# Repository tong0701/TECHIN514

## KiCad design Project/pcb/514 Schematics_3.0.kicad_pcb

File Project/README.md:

# Desk Guardian
### Proximity-based Workspace Awareness System
**TECHIN 514 · Taya (Xintong) Li**

---

## Overview

Desk Guardian is a two-device IoT system that detects how close someone is to your desk and communicates that proximity through a physical gauge and ambient LED — passively, without any interaction required.

In shared workspaces, personal boundaries are often invisible. There is no ambient signal that tells others whether someone is available or focused. Desk Guardian solves this by turning proximity data into a real-time physical display.

---

## System Architecture

Two XIAO ESP32C3 devices communicate over BLE. The sensor device reads distance and classifies proximity state; the display device receives the state and updates the motor pointer and LED accordingly.

```
Sensor Device (BLE Client)          Display Device (BLE Server)
──────────────────────────          ───────────────────────────
XIAO ESP32C3                        XIAO ESP32C3
HC-SR04 Ultrasonic Sensor           28BYJ-48 Stepper Motor + ULN2003
Custom PCB + LiPo Battery           RGB LED + Push Button
                                    Custom PCB + LiPo Battery

TRIG → D9   ECHO → D8               Motor → D0–D3
                                    LED   → D4–D6
                                    BTN   → D10
```

**BLE Config**
- Service UUID: `6f4e0001-1111-2222-3333-444455556666`
- Characteristic UUID: `6f4e0002-1111-2222-3333-444455556666`
- Device name: `Taya_Display_Server`

---

## Proximity States & Logic Flow

| State | Distance | LED | Motor |
|-------|----------|-----|-------|
| SAFE | > 150 cm | Blue (solid) | Pointer left |
| APPROACHING | 45–150 cm | Red (blink) | Pointer center |
| TOO CLOSE | < 45 cm | Red (solid) | Pointer right |

**Auto-reset:** TOO CLOSE held for 3s with no change → auto-send APPROACHING + 5s cooldown. If person leaves → immediate reset to SAFE.

**Hysteresis:** TOO CLOSE exits at > 60 cm · SAFE exits at < 130 cm — prevents state flickering at threshold boundaries.

---

## Hardware

### Sensor Device

### Display Device

| Component | Qty | Notes |
|-----------|-----|-------|
| Seeed Studio XIAO ESP32C3 | 2 | One per device |
| HC-SR04 Ultrasonic Sensor | 1 | Sensor device |
| 28BYJ-48 Stepper + ULN2003 | 1 | Display device |
| 3.7V 1000mAh LiPo Battery | 2 | One per device |
| Custom PCB | 2 | KiCad, lab-fabricated |
| RGB LED | 1 | Display device (green channel non-functional in v1) |
| Push Button | 1 | On/off toggle |

**Power note:** Display device draws ~340mA peak (stepper active). USB power required during use. Future iteration will upsize battery capacity.

---

## Build Photos

| Both Devices | Sensor PCB | Sensor PCB |
|---|---|---|
|  |  |  |

| Display Internal | Display Internal | Sensor Enclosure |
|---|---|---|
|  |  |  |

| Display Enclosure | Display Enclosure |
|---|---|
|  |  |

---

## Signal Processing Pipeline

1. **Read** — HC-SR04 polled every 100ms via TRIG/ECHO GPIO
2. **Smooth** — 3-sample moving average; timeouts filled with last valid reading
3. **Classify** — State machine with hysteresis applied
4. **Send** — BLE characteristic write, only on state change

---

## Build & Flash

Both devices use PlatformIO with Arduino framework.

```ini
[env:seeed_xiao_esp32c3]
platform = espressif32
board = seeed_xiao_esp32c3
framework = arduino
monitor_speed = 115200
```

Flash display device first, then sensor. Sensor will scan for `Taya_Display_Server` on boot and connect automatically.

---

## Repository Structure

```
Project/
├── README.md
├── code/
│   ├── sensor/          # BLE client, HC-SR04 distance detection
│   │   ├── main.cpp
│   │   └── platformio.ini
│   └── display/         # BLE server, stepper + LED control
│       ├── main.cpp
│       └── platformio.ini
├── schematic/           # KiCad schematic files
├── pcb/                 # KiCad PCB layout files
├── cad/                 # 3D print STL files
├── ppt/                 # Final presentation
├── images/              # Device photos
├── datasheet/           # Component datasheets
└── archive/             # Original proposal and early schematics
```

---

## Known Issues & Future Work

- **Power** — Display device requires USB power; LiPo capacity needs to be upsized
- **Enclosure** — Display enclosure too large; USB port opening at wrong height; sensor aperture too small in v1
- **LED** — Green channel non-functional in v1; limited to red/blue only
- **Thresholds** — Distance thresholds are environment-dependent; future version should support configurable parameters or auto-calibration
- **BLE** — Occasional disconnects; auto-reconnect to be implemented

---

## Demo

[Video Demo](https://drive.google.com/file/d/1y1JuozKeC6GTdT54zdWIaoLAR-elOvjI/view?usp=drive_link)

---

## Original Proposal

[View archived proposal](archive/archive_proposal)

---

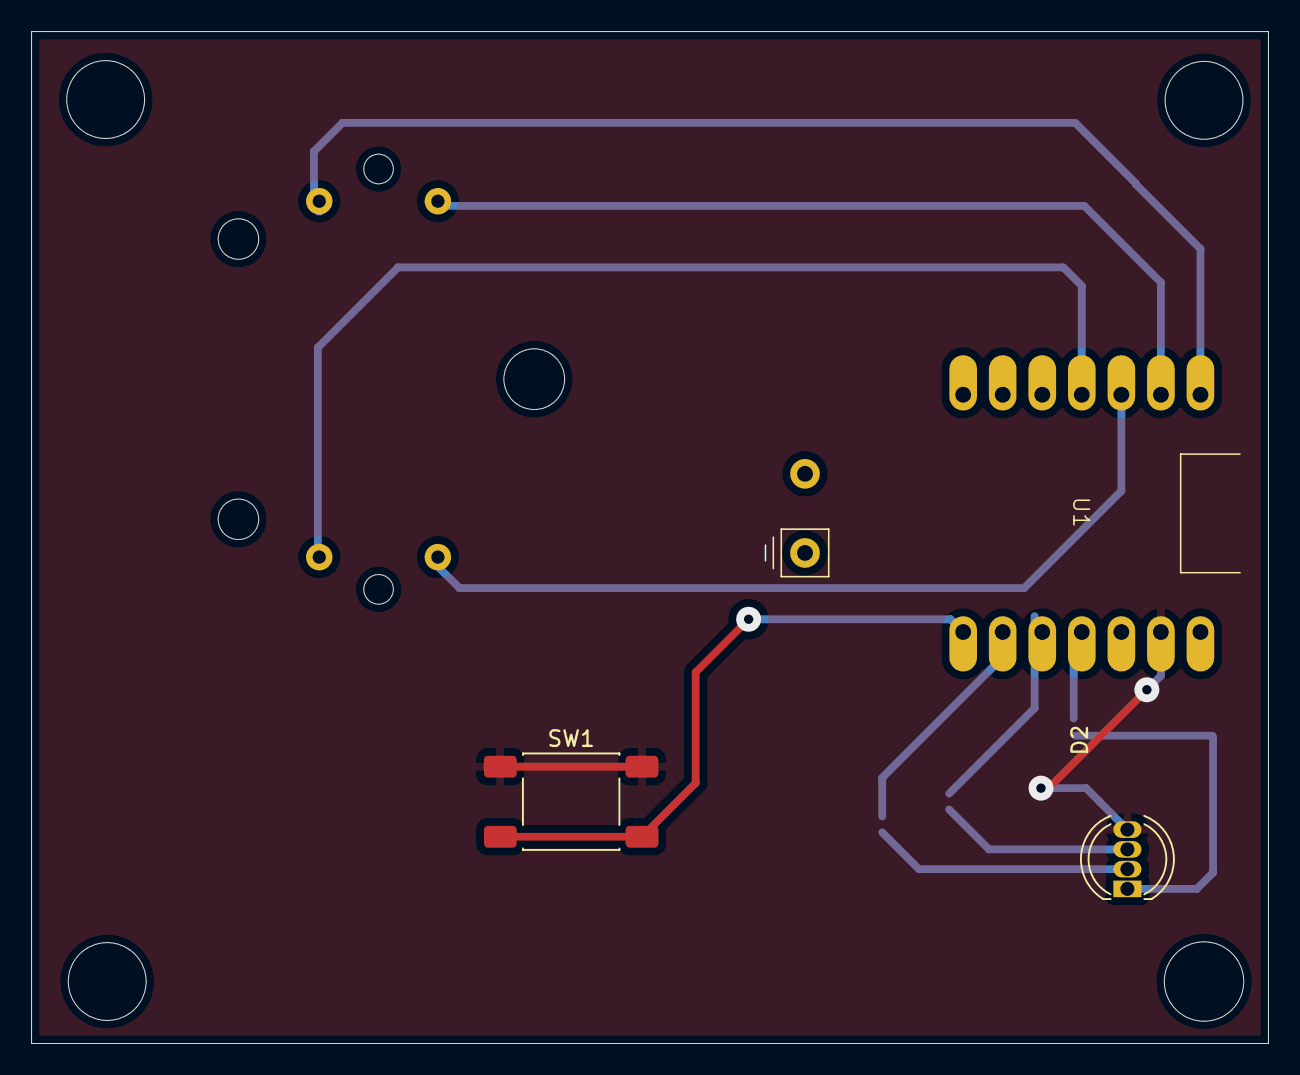
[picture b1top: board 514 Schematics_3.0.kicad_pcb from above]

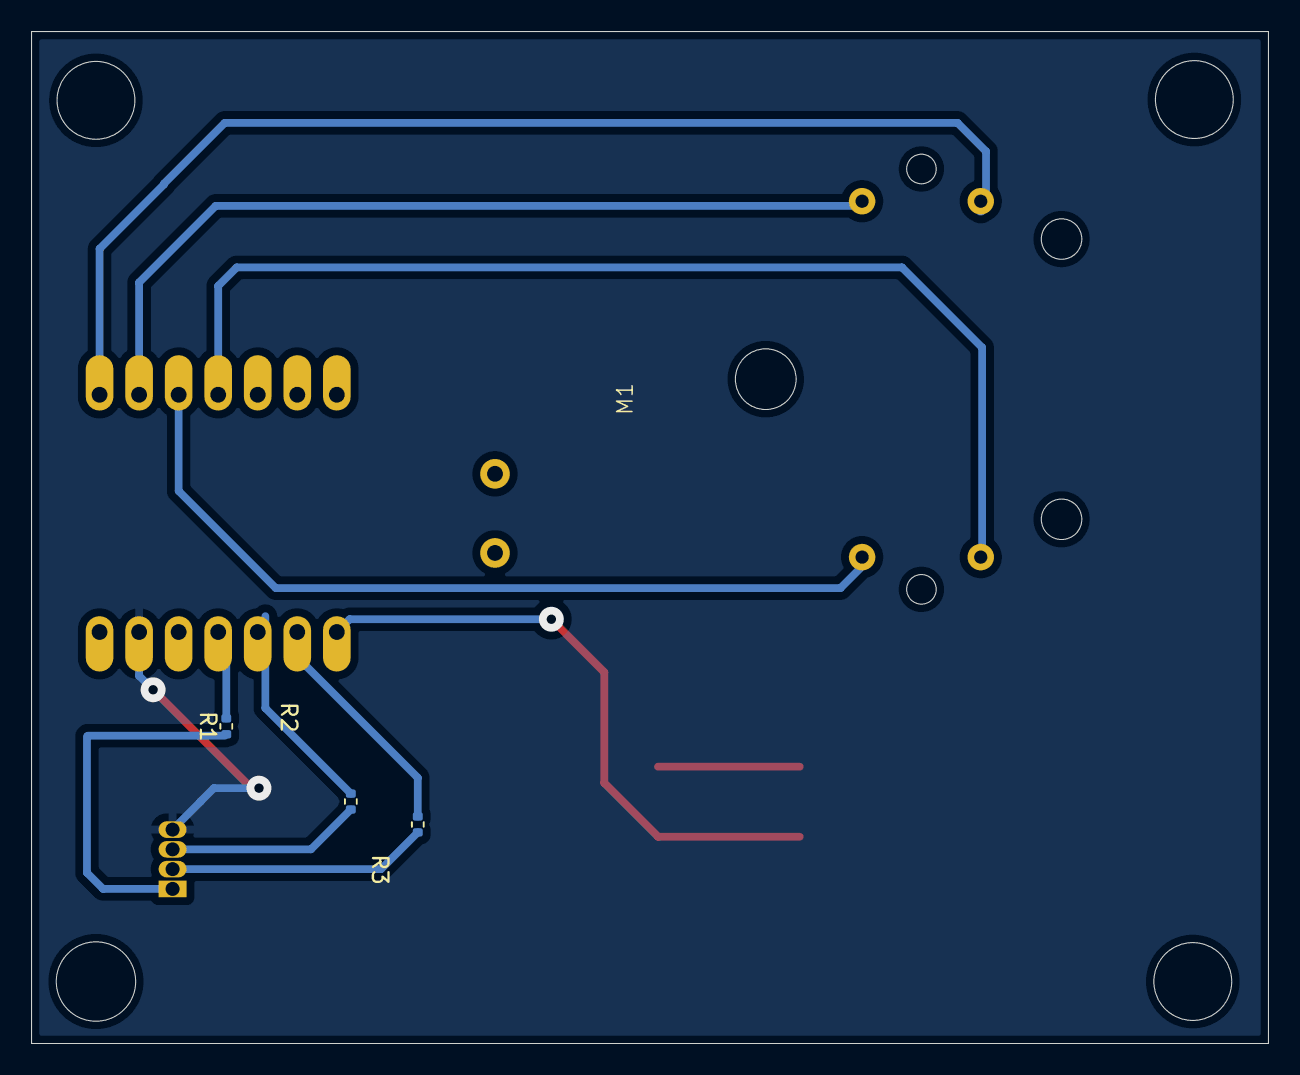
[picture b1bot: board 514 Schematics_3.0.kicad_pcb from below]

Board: 2 copper layers, 79.4 x 65.0 mm, 7 parts (4 on the bottom side), 12 nets.

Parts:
D2: LED_RBGA; LED_D5.0mm-4_RGB
M1: Stepper_Motor_bipolar; x27_stepper_two_holes
R1, R2, R3: R_Small; R_0402_1005Metric
SW1: SW_Push; SW_Push_1P1T_NO_E-Switch_TL3301NxxxxxG
U1: XIAO_ESP32

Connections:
GND: D2.4 (A), SW1.1, U1.13 (GND)
unnamed: D2.2 (BK), R3.1
unnamed: D2.3 (GK), R2.1
unnamed: D2.1 (RK), R1.1
unnamed: M1.2 (-), U1.1 (GPIO1_A0_D0)
unnamed: M1.1, U1.2 (GPIO2_A1_D1)
unnamed: M1.3, U1.3 (GPIO3_A2_D2)
unnamed: M1.4, U1.4 (GPIO4_A3_D3)
unnamed: R3.2, U1.9 (GPIO7_A8_D8_SCK)
unnamed: R2.2, U1.10 (GPIO8_A9_D9_CIPO)
unnamed: R1.2, U1.11 (GPIO9_A10_D10_COPI)
unnamed: SW1.2, U1.8 (GPIO44_D7_RX)

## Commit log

2026-01-05 Add Lab 1 required files
2026-01-05 Clean README for Lab 1
2026-01-05 Remove note about changing board configuration
2026-01-14 Add platformio.ini for Seeed Xiao ESP32C3
2026-01-20 Create 1
2026-01-20 Create noname
2026-01-20 Create 0
2026-01-20 Create techin514_final_sensor_pcb
2026-01-28 Create nonamee
2026-01-28 Create 11
2026-02-07 Add files via upload
    last version
2026-02-12 Create lightbroad
2026-02-22 Create 1.
2026-03-01 Add sensor code for distance measurement and ESP-NOW
2026-03-16 Add desk_guardian_final project for TECHIN514
2026-03-16 Restructure Project: archive old proposal and schematics, promote final project structure
2026-03-16 Rename README (2).md to README.md
2026-03-16 Update README to remove unnecessary program information
    Removed university program details from the README.
